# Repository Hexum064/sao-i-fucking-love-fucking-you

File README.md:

# sao-i-fucking-love-fucking-you

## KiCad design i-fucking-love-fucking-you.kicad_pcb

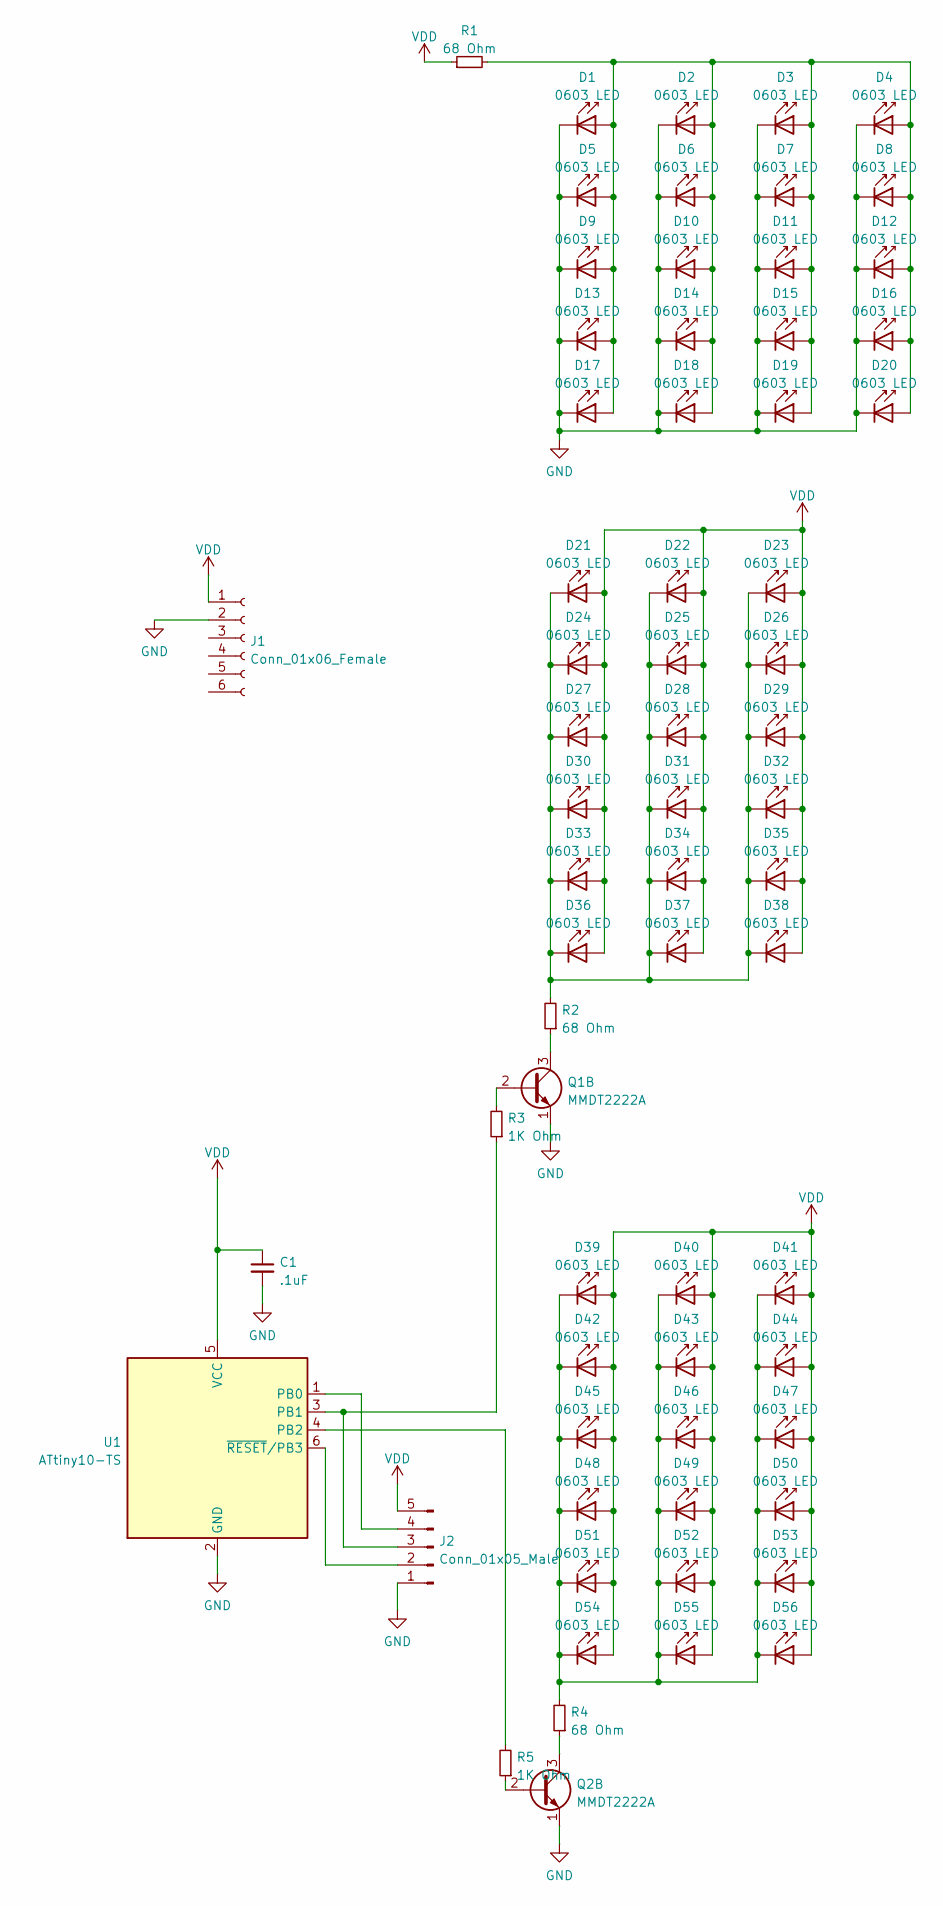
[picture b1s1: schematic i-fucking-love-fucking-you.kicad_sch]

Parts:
C1: .1uF; C_0603_1608Metric_Pad1.08x0.95mm_HandSolder
D1, D2, D3, D4, D5, D6, D7, D8, D9, D10, D11, D12, D13, D14, D15, D16, D17, D18, D19, D20, D21, D22, D23, D24, D25, D26, D27, D28, D29, D30, D31, D32, D33, D34, D35, D36, D37, D38, D39, D40, D41, D42, D43, D44, D45, D46, D47, D48, D49, D50, D51, D52, D53, D54, D55, D56: 0603 LED; LED_0603_1608Metric_Pad1.05x0.95mm_HandSolder
J1: Conn_01x06_Female; PinHeader_2x03_P2.54mm_Vertical
J2: Conn_01x05_Male; PinHeader_1x05_P2.54mm_Vertical
Q1, Q2: MMDT2222A; SOT-23
R1, R2, R4: 68 Ohm; R_0603_1608Metric_Pad0.98x0.95mm_HandSolder
R3, R5: 1K Ohm; R_0603_1608Metric_Pad0.98x0.95mm_HandSolder
U1: ATtiny10-TS; SOT-23-6

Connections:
GND: C1.2, D1.1 (K), D2.1 (K), D3.1 (K), D4.1 (K), D5.1 (K), D6.1 (K), D7.1 (K), D8.1 (K), D9.1 (K), D10.1 (K), D11.1 (K), D12.1 (K), D13.1 (K), D14.1 (K), D15.1 (K), D16.1 (K), D17.1 (K), D18.1 (K), D19.1 (K), D20.1 (K), J1.2, J2.1, Q1.1 (E2), Q2.1 (E2), U1.2 (GND)
unnamed: D1.2 (A), D2.2 (A), D3.2 (A), D4.2 (A), D5.2 (A), D6.2 (A), D7.2 (A), D8.2 (A), D9.2 (A), D10.2 (A), D11.2 (A), D12.2 (A), D13.2 (A), D14.2 (A), D15.2 (A), D16.2 (A), D17.2 (A), D18.2 (A), D19.2 (A), D20.2 (A), R1.2
unnamed: D21.1 (K), D22.1 (K), D23.1 (K), D24.1 (K), D25.1 (K), D26.1 (K), D27.1 (K), D28.1 (K), D29.1 (K), D30.1 (K), D31.1 (K), D32.1 (K), D33.1 (K), D34.1 (K), D35.1 (K), D36.1 (K), D37.1 (K), D38.1 (K), R2.2
unnamed: D39.1 (K), D40.1 (K), D41.1 (K), D42.1 (K), D43.1 (K), D44.1 (K), D45.1 (K), D46.1 (K), D47.1 (K), D48.1 (K), D49.1 (K), D50.1 (K), D51.1 (K), D52.1 (K), D53.1 (K), D54.1 (K), D55.1 (K), D56.1 (K), R4.2
unnamed: J2.2, U1.6 (~RESET/PB3)
unnamed: J2.3, R3.1, U1.3 (PB1)
unnamed: J2.4, U1.1 (PB0)
unnamed: Q1.2 (B2), R3.2
unnamed: Q1.3 (C2), R2.1
unnamed: Q2.2 (B2), R5.1
unnamed: Q2.3 (C2), R4.1
unnamed: R5.2, U1.4 (PB2)
VDD: C1.1, D21.2 (A), D22.2 (A), D23.2 (A), D24.2 (A), D25.2 (A), D26.2 (A), D27.2 (A), D28.2 (A), D29.2 (A), D30.2 (A), D31.2 (A), D32.2 (A), D33.2 (A), D34.2 (A), D35.2 (A), D36.2 (A), D37.2 (A), D38.2 (A), D39.2 (A), D40.2 (A), D41.2 (A), D42.2 (A), D43.2 (A), D44.2 (A), D45.2 (A), D46.2 (A), D47.2 (A), D48.2 (A), D49.2 (A), D50.2 (A), D51.2 (A), D52.2 (A), D53.2 (A), D54.2 (A), D55.2 (A), D56.2 (A), J1.1, J2.5, R1.1, U1.5 (VCC)

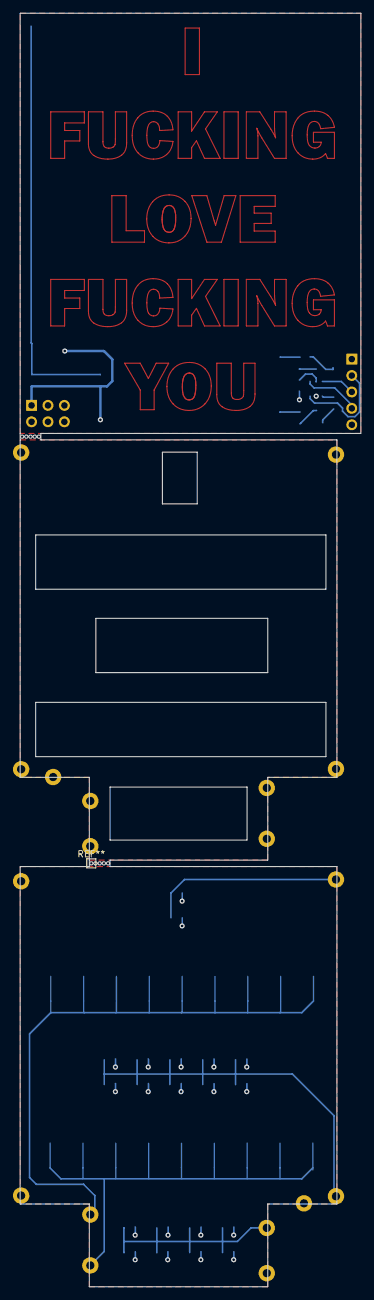
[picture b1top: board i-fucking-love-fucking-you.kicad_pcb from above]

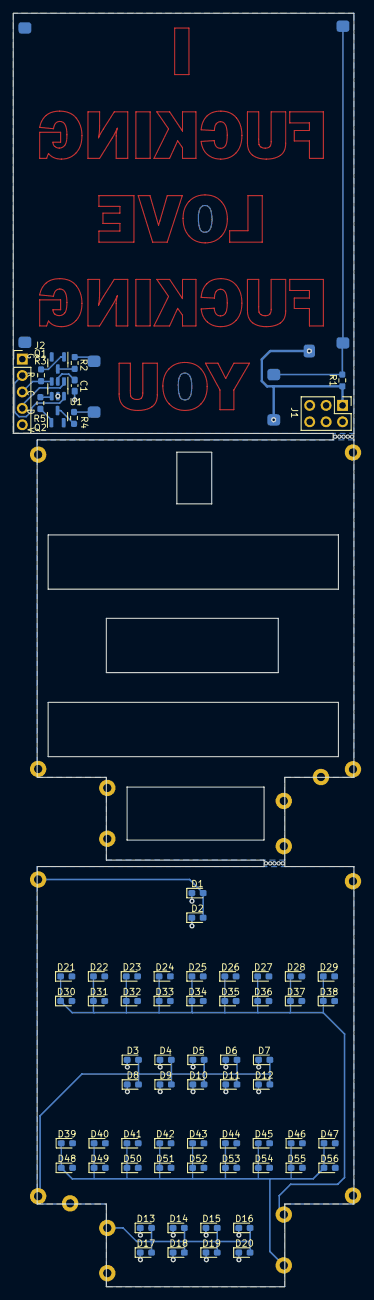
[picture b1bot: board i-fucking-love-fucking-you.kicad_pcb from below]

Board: 2 copper layers, 52.7 x 197.0 mm, 67 parts (67 on the bottom side), 13 nets.

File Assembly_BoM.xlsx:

*Ref Des | Manufacturer/Brand | *Mfg Part # | *Package | *Description / Value
D1 | https://lcsc.com/product-detail/Light-Emitting-Diodes-span-s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 | SZYY0603R | 0603 | Red 0603 LED
D2 | https://lcsc.com/product-detail/Light-Emitting-Diodes-span-s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 | SZYY0603R | 0603 | Red 0603 LED
D3 | https://lcsc.com/product-detail/Light-Emitting-Diodes-span-s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 | SZYY0603R | 0603 | Red 0603 LED
D4 | https://lcsc.com/product-detail/Light-Emitting-Diodes-span-s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 | SZYY0603R | 0603 | Red 0603 LED
D5 | https://lcsc.com/product-detail/Light-Emitting-Diodes-span-s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 | SZYY0603R | 0603 | Red 0603 LED
D6 | https://lcsc.com/product-detail/Light-Emitting-Diodes-span-s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 | SZYY0603R | 0603 | Red 0603 LED
D7 | https://lcsc.com/product-detail/Light-Emitting-Diodes-span-s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 | SZYY0603R | 0603 | Red 0603 LED
D8 | https://lcsc.com/product-detail/Light-Emitting-Diodes-span-s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 | SZYY0603R | 0603 | Red 0603 LED
D9 | https://lcsc.com/product-detail/Light-Emitting-Diodes-span-s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 | SZYY0603R | 0603 | Red 0603 LED
D10 | https://lcsc.com/product-detail/Light-Emitting-Diodes-span-s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 | SZYY0603R | 0603 | Red 0603 LED
D11 | https://lcsc.com/product-detail/Light-Emitting-Diodes-span-s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 | SZYY0603R | 0603 | Red 0603 LED
D12 | https://lcsc.com/product-detail/Light-Emitting-Diodes-span-s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 | SZYY0603R | 0603 | Red 0603 LED
D13 | https://lcsc.com/product-detail/Light-Emitting-Diodes-span-s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 | SZYY0603R | 0603 | Red 0603 LED
D14 | https://lcsc.com/product-detail/Light-Emitting-Diodes-span-s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 | SZYY0603R | 0603 | Red 0603 LED
D15 | https://lcsc.com/product-detail/Light-Emitting-Diodes-span-s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 | SZYY0603R | 0603 | Red 0603 LED
D16 | https://lcsc.com/product-detail/Light-Emitting-Diodes-span-s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 | SZYY0603R | 0603 | Red 0603 LED
D17 | https://lcsc.com/product-detail/Light-Emitting-Diodes-span-s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 | SZYY0603R | 0603 | Red 0603 LED
D18 | https://lcsc.com/product-detail/Light-Emitting-Diodes-span-s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 | SZYY0603R | 0603 | Red 0603 LED
D19 | https://lcsc.com/product-detail/Light-Emitting-Diodes-span-s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 | SZYY0603R | 0603 | Red 0603 LED
D20 | https://lcsc.com/product-detail/Light-Emitting-Diodes-span-s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 | SZYY0603R | 0603 | Red 0603 LED
D21 | https://lcsc.com/product-detail/Light-Emitting-Diodes-span-s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 | SZYY0603R | 0603 | Red 0603 LED
D22 | https://lcsc.com/product-detail/Light-Emitting-Diodes-span-s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 | SZYY0603R | 0603 | Red 0603 LED
D23 | https://lcsc.com/product-detail/Light-Emitting-Diodes-span-s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 | SZYY0603R | 0603 | Red 0603 LED
D24 | https://lcsc.com/product-detail/Light-Emitting-Diodes-span-s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 | SZYY0603R | 0603 | Red 0603 LED
D25 | https://lcsc.com/product-detail/Light-Emitting-Diodes-span-s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 | SZYY0603R | 0603 | Red 0603 LED
D26 | https://lcsc.com/product-detail/Light-Emitting-Diodes-span-s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 | SZYY0603R | 0603 | Red 0603 LED
D27 | https://lcsc.com/product-detail/Light-Emitting-Diodes-span-s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 | SZYY0603R | 0603 | Red 0603 LED
D28 | https://lcsc.com/product-detail/Light-Emitting-Diodes-span-s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 | SZYY0603R | 0603 | Red 0603 LED
D29 | https://lcsc.com/product-detail/Light-Emitting-Diodes-span-s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 | SZYY0603R | 0603 | Red 0603 LED
D30 | https://lcsc.com/product-detail/Light-Emitting-Diodes-span-s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 | SZYY0603R | 0603 | Red 0603 LED
D31 | https://lcsc.com/product-detail/Light-Emitting-Diodes-span-s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 | SZYY0603R | 0603 | Red 0603 LED
D32 | https://lcsc.com/product-detail/Light-Emitting-Diodes-span-s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 | SZYY0603R | 0603 | Red 0603 LED
D33 | https://lcsc.com/product-detail/Light-Emitting-Diodes-span-s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 | SZYY0603R | 0603 | Red 0603 LED
D34 | https://lcsc.com/product-detail/Light-Emitting-Diodes-span-s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 | SZYY0603R | 0603 | Red 0603 LED
D35 | https://lcsc.com/product-detail/Light-Emitting-Diodes-span-s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 | SZYY0603R | 0603 | Red 0603 LED
D36 | https://lcsc.com/product-detail/Light-Emitting-Diodes-span-s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 | SZYY0603R | 0603 | Red 0603 LED
D37 | https://lcsc.com/product-detail/Light-Emitting-Diodes-span-s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 | SZYY0603R | 0603 | Red 0603 LED
D38 | https://lcsc.com/product-detail/Light-Emitting-Diodes-span-s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 | SZYY0603R | 0603 | Red 0603 LED
D39 | https://lcsc.com/product-detail/Light-Emitting-Diodes-span-s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 | SZYY0603R | 0603 | Red 0603 LED
D40 | https://lcsc.com/product-detail/Light-Emitting-Diodes-span-s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 | SZYY0603R | 0603 | Red 0603 LED
D41 | https://lcsc.com/product-detail/Light-Emitting-Diodes-span-s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 | SZYY0603R | 0603 | Red 0603 LED
D42 | https://lcsc.com/product-detail/Light-Emitting-Diodes-span-s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 | SZYY0603R | 0603 | Red 0603 LED
D43 | https://lcsc.com/product-detail/Light-Emitting-Diodes-span-s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 | SZYY0603R | 0603 | Red 0603 LED
D44 | https://lcsc.com/product-detail/Light-Emitting-Diodes-span-s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 | SZYY0603R | 0603 | Red 0603 LED
D45 | https://lcsc.com/product-detail/Light-Emitting-Diodes-span-s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 | SZYY0603R | 0603 | Red 0603 LED
D46 | https://lcsc.com/product-detail/Light-Emitting-Diodes-span-s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 | SZYY0603R | 0603 | Red 0603 LED
D47 | https://lcsc.com/product-detail/Light-Emitting-Diodes-span-s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 | SZYY0603R | 0603 | Red 0603 LED
D48 | https://lcsc.com/product-detail/Light-Emitting-Diodes-span-s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 | SZYY0603R | 0603 | Red 0603 LED
D49 | https://lcsc.com/product-detail/Light-Emitting-Diodes-span-s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 | SZYY0603R | 0603 | Red 0603 LED
D50 | https://lcsc.com/product-detail/Light-Emitting-Diodes-span-s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 | SZYY0603R | 0603 | Red 0603 LED
D51 | https://lcsc.com/product-detail/Light-Emitting-Diodes-span-s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 | SZYY0603R | 0603 | Red 0603 LED
D52 | https://lcsc.com/product-detail/Light-Emitting-Diodes-span-s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 | SZYY0603R | 0603 | Red 0603 LED
D53 | https://lcsc.com/product-detail/Light-Emitting-Diodes-span-s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 | SZYY0603R | 0603 | Red 0603 LED
D54 | https://lcsc.com/product-detail/Light-Emitting-Diodes-span-s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 | SZYY0603R | 0603 | Red 0603 LED
D55 | https://lcsc.com/product-detail/Light-Emitting-Diodes-span-s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 | SZYY0603R | 0603 | Red 0603 LED
D56 | https://lcsc.com/product-detail/Light-Emitting-Diodes-span-s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 | SZYY0603R | 0603 | Red 0603 LED
C1 | https://lcsc.com/product-detail/Multilayer-Ceramic-Capacitor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 | TCC0603X7R104K500CT | 0603 | 100nF Capacitor
R1 | https://lcsc.com/product-detail/Chip-Resistor-Surface-Mount_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 | ERJPA3J680V | 0603 | 68 Ohm resistor
R2 | https://lcsc.com/product-detail/Chip-Resistor-Surface-Mount_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 | ERJPA3J680V | 0603 | 68 Ohm resistor
R3 | https://lcsc.com/product-detail/Chip-Resistor-Surface-Mount_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 | ERJPA3J102V | 0603 | 1k Ohm resistor
R4 | https://lcsc.com/product-detail/Chip-Resistor-Surface-Mount_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 | ERJPA3J680V | 0603 | 68 Ohm resistor
R5 | https://lcsc.com/product-detail/Chip-Resistor-Surface-Mount_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 | ERJPA3J102V | 0603 | 1k Ohm resistor
Q1 | https://lcsc.com/product-detail/Bipolar-Transistors-BJT_PANJ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 | MMBT2222A | SOT-23 | npn bjt transistor
Q2 | https://lcsc.com/product-detail/Bipolar-Transistors-BJT_PANJ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 | MMBT2222A | SOT-23 | npn bjt transistor
U1 | https://lcsc.com/product-detail/MICROCHIP_Microchip-Tech-ATT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 | ATTINY10-TSHR | SOT-23-6 | Microchip ATTiny10 microcontroller

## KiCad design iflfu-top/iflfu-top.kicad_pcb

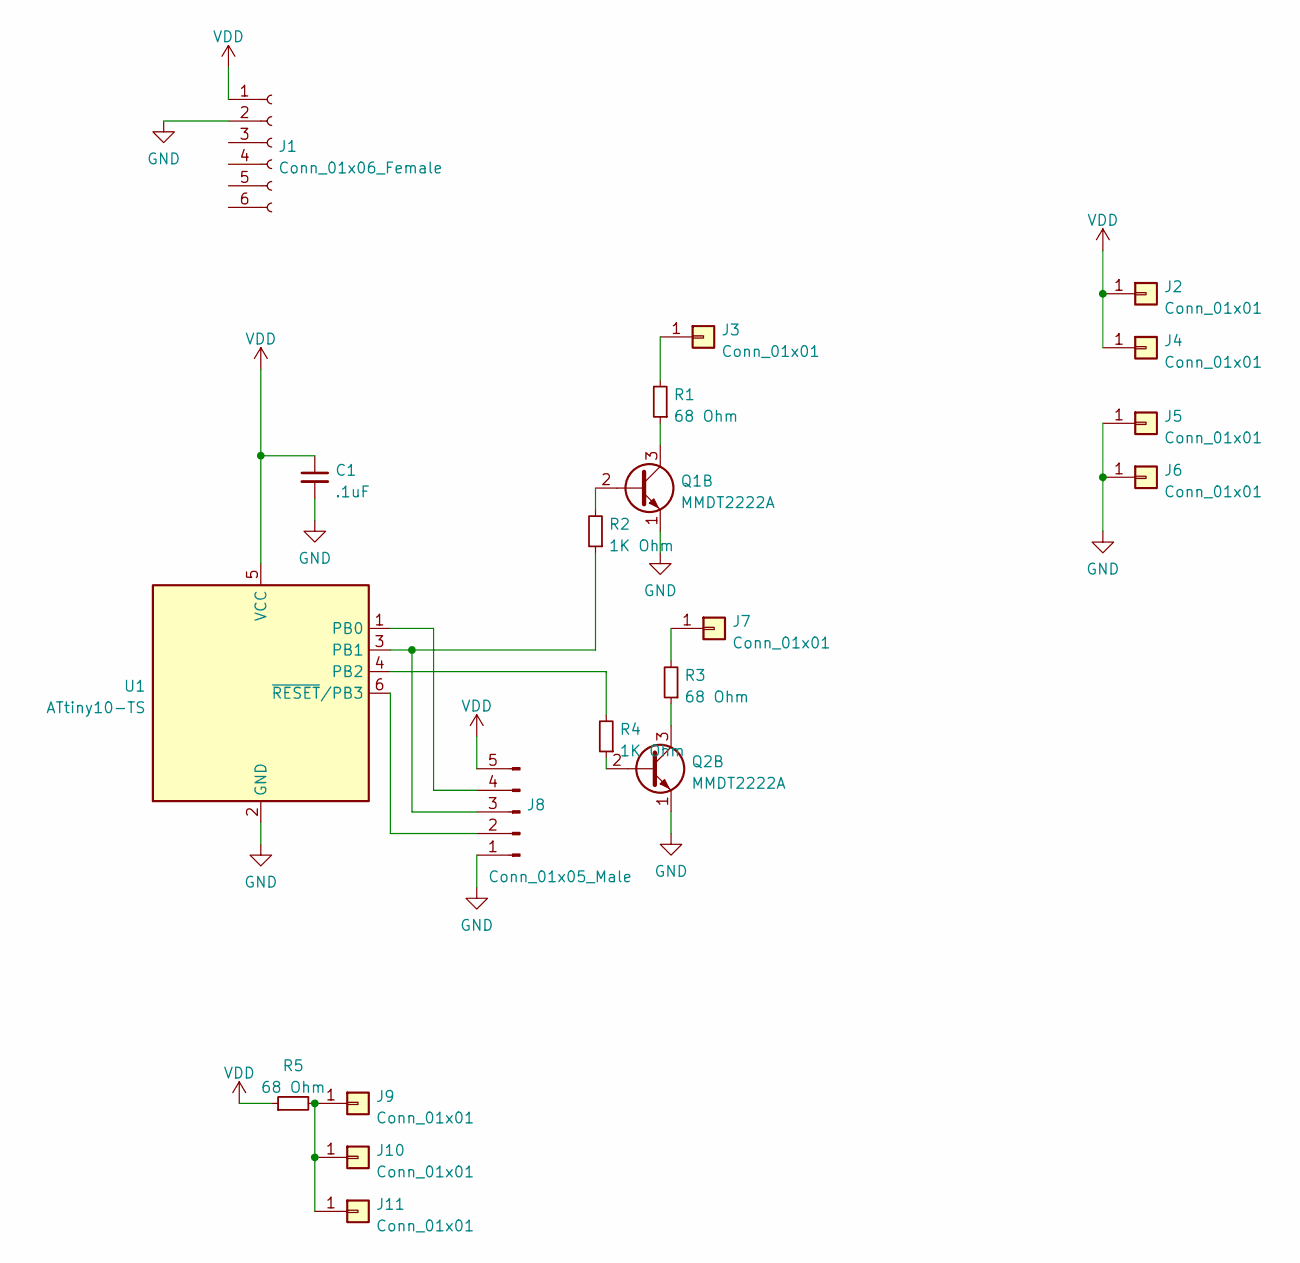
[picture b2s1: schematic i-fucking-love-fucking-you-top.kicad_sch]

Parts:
C1: .1uF; C_0603_1608Metric_Pad1.08x0.95mm_HandSolder
J1: Conn_01x06_Female; PinHeader_2x03_P2.54mm_Vertical
J2, J3, J4, J5, J6, J7, J9, J10, J11: Conn_01x01; TestPoint_Pad_2.0x2.0mm
J8: Conn_01x05_Male; PinHeader_1x05_P2.54mm_Vertical
Q1, Q2: MMDT2222A; SOT-23
R1, R3, R5: 68 Ohm; R_0603_1608Metric_Pad0.98x0.95mm_HandSolder
R2, R4: 1K Ohm; R_0603_1608Metric_Pad0.98x0.95mm_HandSolder
U1: ATtiny10-TS; SOT-23-6

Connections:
GND: C1.2, J1.2, J5.1, J6.1, J8.1, Q1.1 (E2), Q2.1 (E2), U1.2 (GND)
unnamed: J3.1, R1.2
unnamed: J7.1, R3.2
unnamed: J8.2, U1.6 (~RESET/PB3)
unnamed: J8.3, R2.1, U1.3 (PB1)
unnamed: J8.4, U1.1 (PB0)
unnamed: J9.1, J10.1, J11.1, R5.2
unnamed: Q1.2 (B2), R2.2
unnamed: Q1.3 (C2), R1.1
unnamed: Q2.2 (B2), R4.1
unnamed: Q2.3 (C2), R3.1
unnamed: R4.2, U1.4 (PB2)
VDD: C1.1, J1.1, J2.1, J4.1, J8.5, R5.1, U1.5 (VCC)

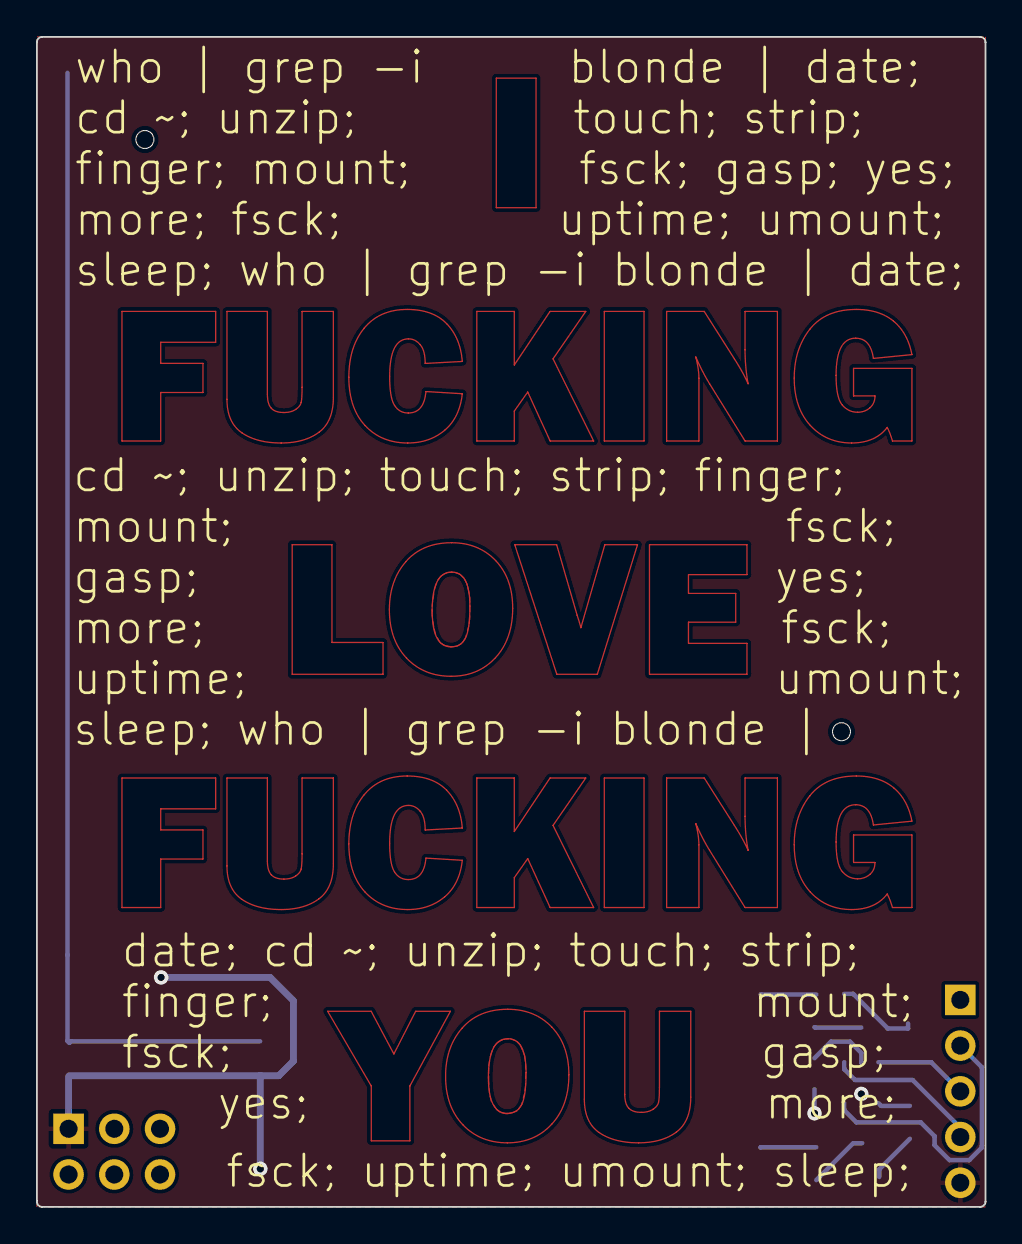
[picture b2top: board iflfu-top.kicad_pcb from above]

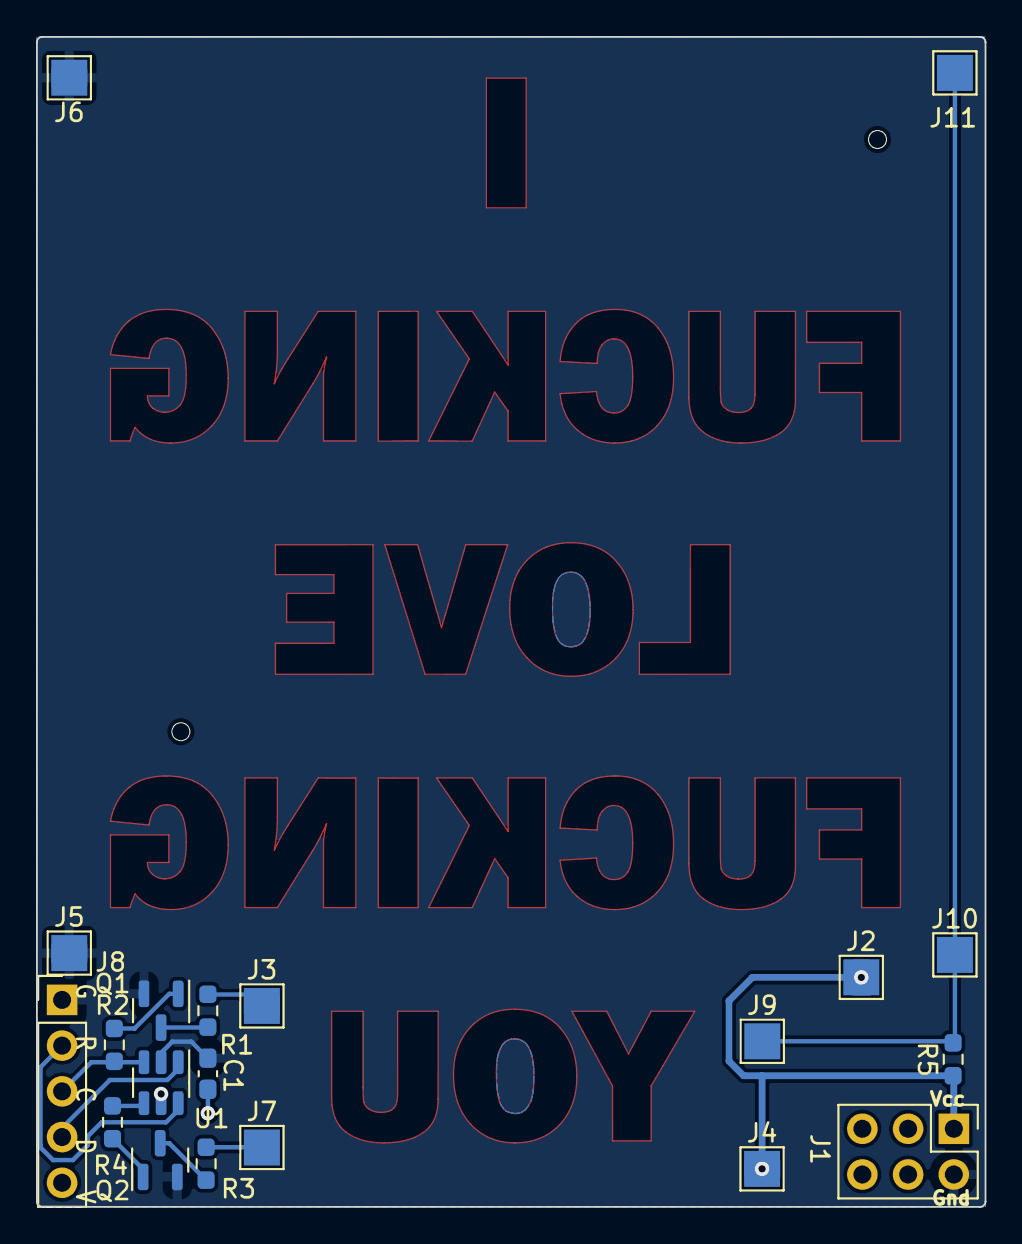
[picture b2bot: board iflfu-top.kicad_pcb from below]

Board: 2 copper layers, 52.7 x 65.0 mm, 20 parts (20 on the bottom side), 13 nets.

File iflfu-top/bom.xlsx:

Comment | Designator | Footprint | JLCPCB Part #
npnbjttransistor | Q2,Q1 | https://lcsc.com/product-detail/Bipolar-Transistors-BJT_PANJ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 | C181121
MicrochipATTiny10microcontroller | U1 | https://lcsc.com/product-detail/MICROCHIP_Microchip-Tech-ATT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 | C128438
100nFCapacitor | C1 | https://lcsc.com/product-detail/Multilayer-Ceramic-Capacitor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 | C282519
68Ohmresistor | R1,R3,R5 | https://lcsc.com/product-detail/Chip-Resistor-Surface-Mount_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 | C445804
1kOhmresistor | R2,R4 | https://lcsc.com/product-detail/Chip-Resistor-Surface-Mount_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 | C881173
2x3 2.54mm pin header | J1 | https://lcsc.com/product-detail/Pin-Headers_BOOMELE-Boom-Pre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 | C65114

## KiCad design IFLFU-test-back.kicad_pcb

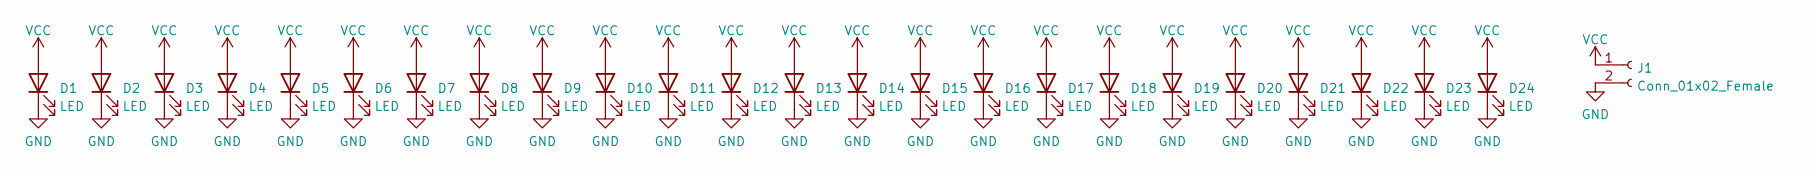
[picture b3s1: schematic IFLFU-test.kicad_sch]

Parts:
D1, D2, D3, D4, D5, D6, D7, D8, D9, D10, D11, D12, D13, D14, D15, D16, D17, D18, D19, D20, D21, D22, D23, D24: LED; LED_0603_1608Metric
J1: Conn_01x02_Female; PinHeader_1x02_P2.54mm_Vertical

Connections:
GND: D1.1 (K), D2.1 (K), D3.1 (K), D4.1 (K), D5.1 (K), D6.1 (K), D7.1 (K), D8.1 (K), D9.1 (K), D10.1 (K), D11.1 (K), D12.1 (K), D13.1 (K), D14.1 (K), D15.1 (K), D16.1 (K), D17.1 (K), D18.1 (K), D19.1 (K), D20.1 (K), D21.1 (K), D22.1 (K), D23.1 (K), D24.1 (K), J1.2
VCC: D1.2 (A), D2.2 (A), D3.2 (A), D4.2 (A), D5.2 (A), D6.2 (A), D7.2 (A), D8.2 (A), D9.2 (A), D10.2 (A), D11.2 (A), D12.2 (A), D13.2 (A), D14.2 (A), D15.2 (A), D16.2 (A), D17.2 (A), D18.2 (A), D19.2 (A), D20.2 (A), D21.2 (A), D22.2 (A), D23.2 (A), D24.2 (A), J1.1

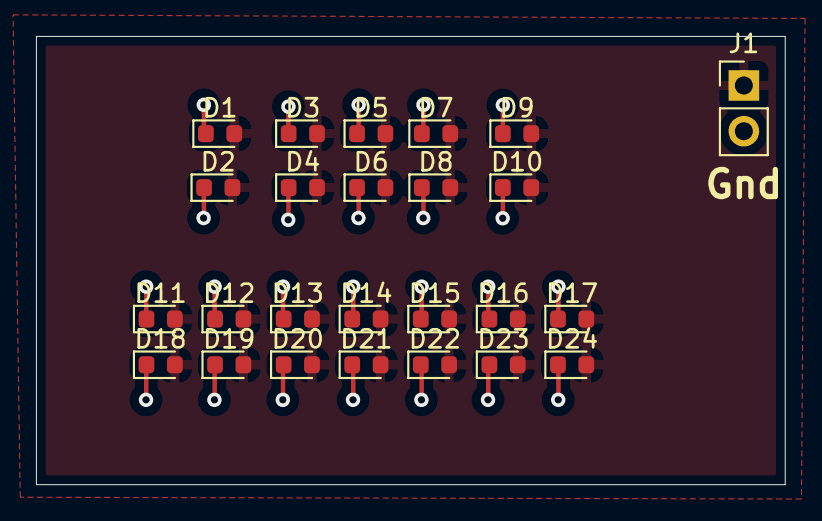
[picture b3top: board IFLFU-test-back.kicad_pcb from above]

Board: 2 copper layers, 41.6 x 24.9 mm, 25 parts (0 on the bottom side), 2 nets.

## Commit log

2022-06-20 added code to do rand from adc on start
2022-06-25 gerber updates and sanity checkin
